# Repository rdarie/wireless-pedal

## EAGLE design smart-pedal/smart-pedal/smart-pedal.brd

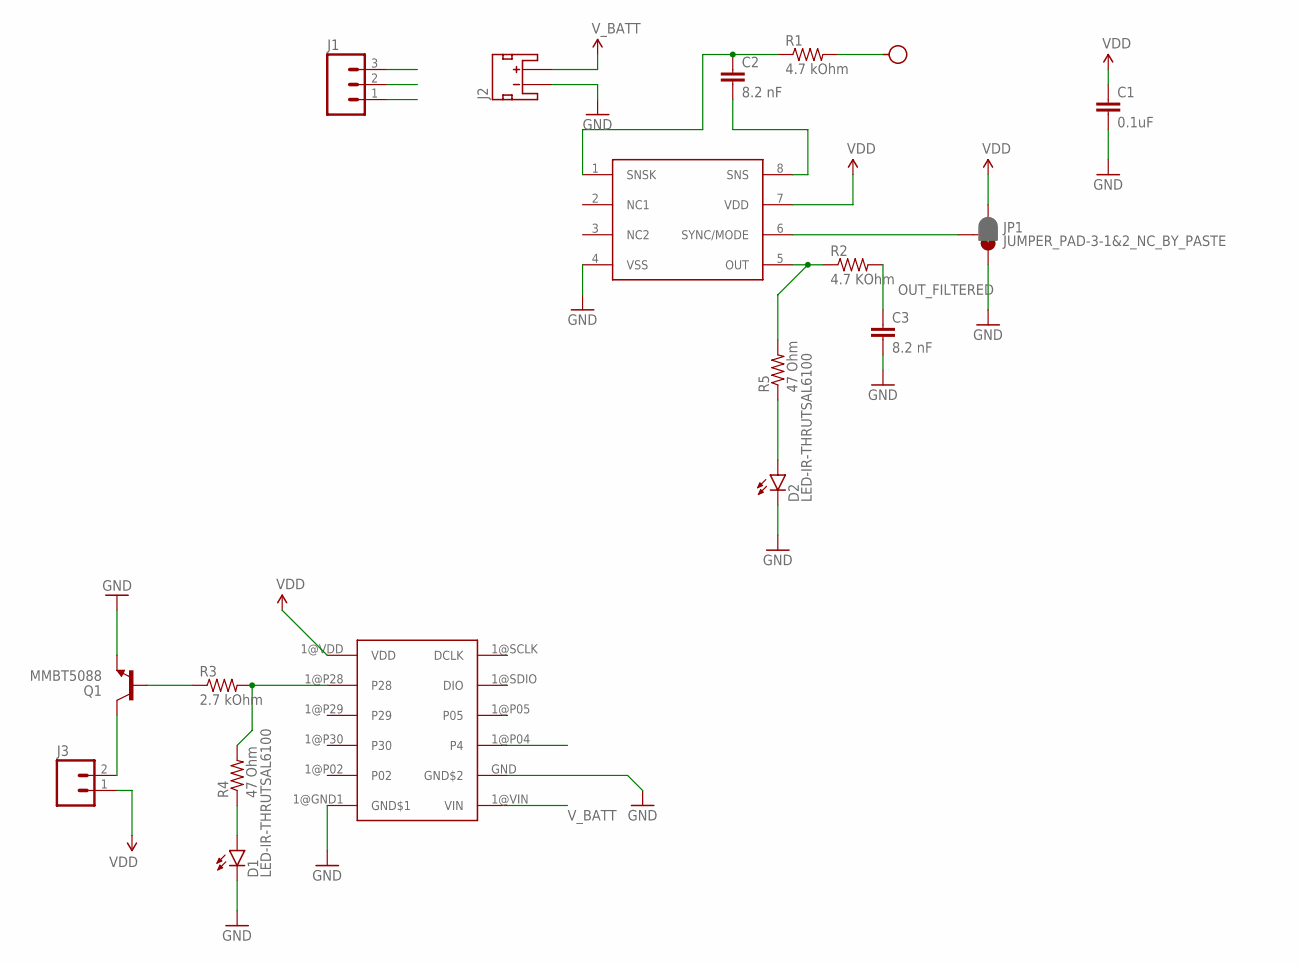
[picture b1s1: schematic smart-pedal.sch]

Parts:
C1: 0.1uF; 0603-CAP
C2, C3: 8.2 nF; 0603-CAP
D1, D2: LED-IR-THRUTSAL6100; LED5MM
H1: SEW_HOLE-SMALL; SIMPLE_HOLE_SM
J1: M03LOCK; 1X03_LOCK
J2: JST_2MM_MALE; JST-2-SMD
J3: M02LOCK; 1X02_LOCK
JP1: JUMPER_PAD-3-1&2_NC_BY_PASTE; PAD-HUMPER-3-1&2_NC_BY_PASTE_YES_SILK_FULL_BOX
Q1: MMBT5088; SOT23-3
R1: 4.7 kOhm; 0603-RES
R2: 4.7 KOhm; 0603-RES
R3: 2.7 kOhm; 0603-RES
R4, R5: 47 Ohm; 0603-RES
U$1: AT42QT1011; UDFN8
U$2: NANOV2

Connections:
CAP: H1.P$1, R1.2
GND: C1.2, C3.2, D1.K (C), D2.K (C), J1.1, J2.1 (-), JP1.3, Q1.2 (E), U$1.4 (VSS), U$2.1@GND1 (GND$1), U$2.GND (GND$2)
MOTOR_OUT: J1.3, R3.2, R4.2, U$2.1@P28 (P28)
unnamed: J3.2, Q1.3 (C)
unnamed: Q1.1 (B), R3.1
unnamed: D1.A, R4.1
unnamed: D2.A, R5.1
OUT: R2.1, R5.2, U$1.5 (OUT)
OUT_FILTERED: C3.1, J1.2, R2.2, U$2.1@P04 (P4)
SNS: C2.2, U$1.8 (SNS)
SNSK: C2.1, R1.1, U$1.1 (SNSK)
SYNC: JP1.2, U$1.6 (SYNC/MODE)
VDD: C1.1, J3.1, JP1.1, U$1.7 (VDD), U$2.1@VDD (VDD)
V_BATT: J2.2 (+), U$2.1@VIN (VIN)

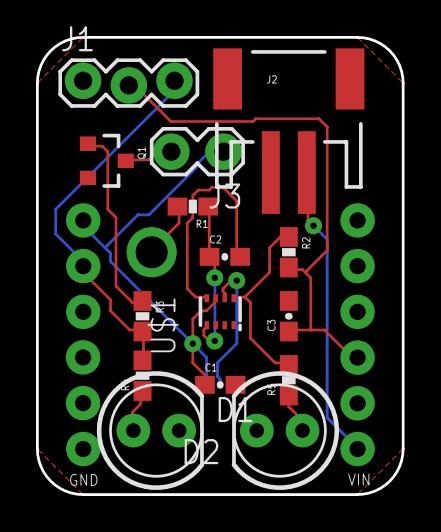
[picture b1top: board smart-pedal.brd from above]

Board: 2 copper layers, 20.3 x 25.4 mm, 18 parts (1 on the bottom side), 14 nets.

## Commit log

2017-02-02 :space_invader: Added .gitattributes & .gitignore files
2017-03-24 added stuff
2017-08-22 hard reset
2017-08-22 started example
2017-08-23 bluetooth
2017-08-25 switched to mbed
2017-08-25 bugfices
2017-08-25 work
2017-08-25 bugfix
2017-08-25 bug fix
2017-08-25 check out data packet structure
2018-01-30 better naming conventions
2018-01-30 renamed some stuff, worked on the circuit schematic
2018-03-23 cleanup

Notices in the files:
parts and their libraries:
SparkFun-Connectors: Licensing: Creative Commons ShareAlike 4.0 International - https://creativecommons.org/licenses/by-sa/4.0
